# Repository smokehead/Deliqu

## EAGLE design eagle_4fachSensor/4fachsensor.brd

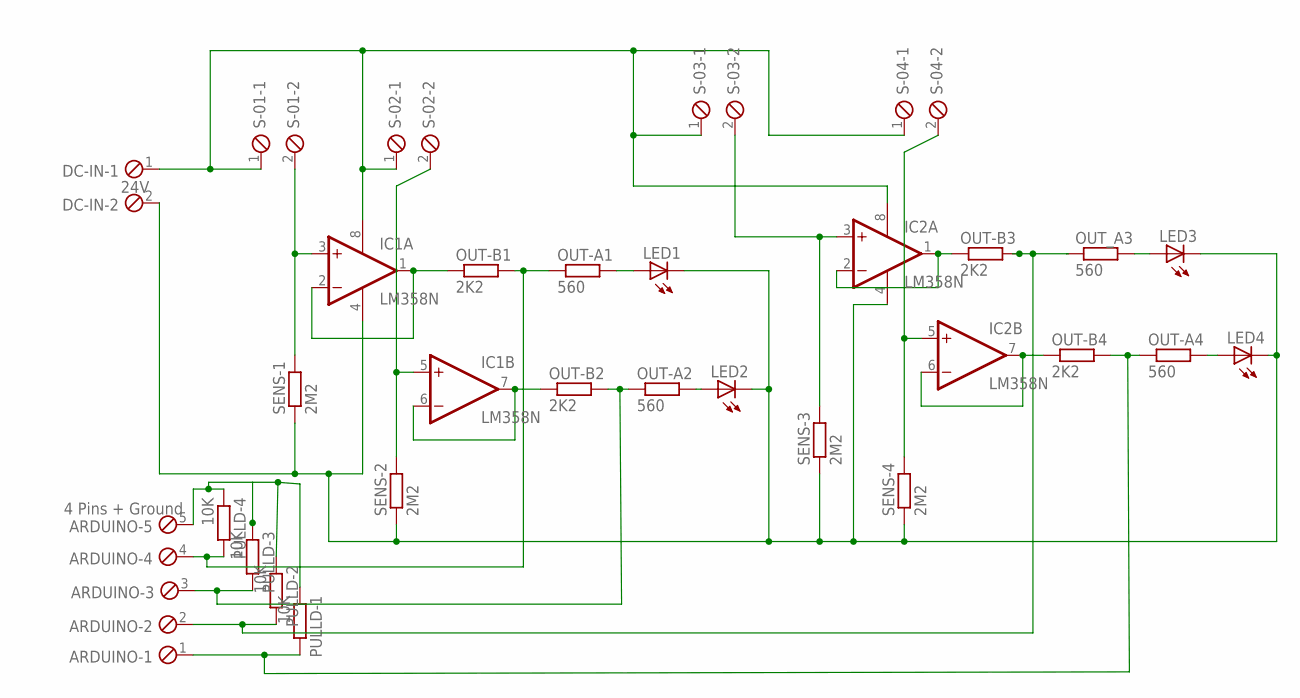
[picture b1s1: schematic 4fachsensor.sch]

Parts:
ARDUINO: 4 Pins + Ground; 5POL254
DC-IN: 24V; 2POL254
IC1, IC2: LM358N; DIL08
LED1, LED2, LED3, LED4: LED5MM
OUT-A1, OUT-A2, OUT-A4: 560; 0207/7
OUT-B1, OUT-B2, OUT-B3, OUT-B4: 2K2; 0207/7
OUT_A3: 560; 0207/7
PULLD-1, PULLD-2, PULLD-3, PULLD-4: 10K; 0207/7
S-01, S-02, S-03, S-04: MPT2; 2POL254
SENS-1, SENS-2, SENS-3, SENS-4: 2M2; 0207/7

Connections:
unnamed: DC-IN.1, IC1.8 (V+), IC2.8 (V+), S-01.1, S-02.1, S-03.1, S-04.1
unnamed: IC1.3 (+IN), S-01.2, SENS-1.2
unnamed: DC-IN.2, IC1.4 (V-), IC2.4 (V-), LED1.K (C), LED2.K (C), LED3.K (C), LED4.K (C), SENS-1.1, SENS-2.1, SENS-3.1, SENS-4.1
unnamed: IC1.1 (OUT), IC1.2 (-IN), OUT-B1.1
unnamed: LED1.A, OUT-A1.2
unnamed: IC1.6 (-IN), IC1.7 (OUT), OUT-B2.1
unnamed: IC1.5 (+IN), S-02.2, SENS-2.2
unnamed: LED2.A, OUT-A2.2
unnamed: LED4.A, OUT-A4.2
unnamed: IC2.3 (+IN), S-03.2, SENS-3.2
unnamed: IC2.5 (+IN), S-04.2, SENS-4.2
unnamed: ARDUINO.1, OUT-A4.1, OUT-B4.2, PULLD-1.2
unnamed: ARDUINO.2, OUT-B3.2, OUT_A3.1, PULLD-2.2
unnamed: IC2.1 (OUT), IC2.2 (-IN), OUT-B3.1
unnamed: IC2.6 (-IN), IC2.7 (OUT), OUT-B4.1
unnamed: ARDUINO.3, OUT-A2.1, OUT-B2.2, PULLD-3.2
unnamed: LED3.A, OUT_A3.2
unnamed: ARDUINO.4, OUT-A1.1, OUT-B1.2, PULLD-4.2
unnamed: ARDUINO.5, PULLD-1.1, PULLD-2.1, PULLD-3.1, PULLD-4.1

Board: 2 copper layers, 28 parts (0 on the bottom side), 19 nets, no tracks yet.

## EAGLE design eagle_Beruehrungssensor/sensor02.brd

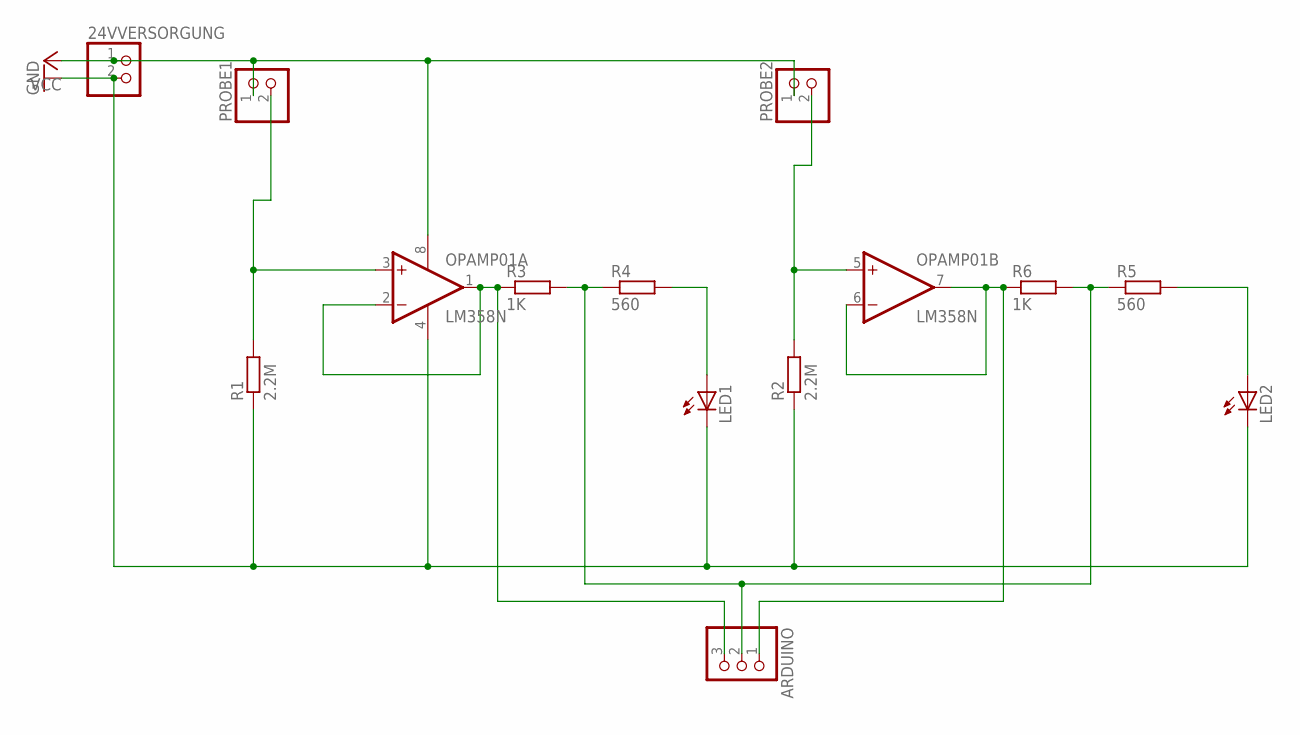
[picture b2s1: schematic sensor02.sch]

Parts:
24VVERSORGUNG: PINHD-1X2; 1X02
ARDUINO: PINHD-1X3; 1X03
LED1, LED2: LED5MM
OPAMP01: LM358N; DIL08
PROBE1, PROBE2: PINHD-1X2; 1X02
R1, R2: 2.2M; 0207/7
R3, R6: 1K; 0207/7
R4, R5: 560; 0207/7

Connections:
GND: 24VVERSORGUNG.2, LED1.K (C), LED2.K (C), OPAMP01.4 (V-), R1.1, R2.1
unnamed: OPAMP01.3 (+IN), PROBE1.2, R1.2
unnamed: OPAMP01.5 (+IN), PROBE2.2, R2.2
unnamed: ARDUINO.3, OPAMP01.1 (OUT), OPAMP01.2 (-IN), R3.1
unnamed: LED1.A, R4.2
unnamed: ARDUINO.1, OPAMP01.6 (-IN), OPAMP01.7 (OUT), R6.1
unnamed: ARDUINO.2, R3.2, R4.1, R5.1, R6.2
unnamed: LED2.A, R5.2
VCC: 24VVERSORGUNG.1, OPAMP01.8 (V+), PROBE1.1, PROBE2.1

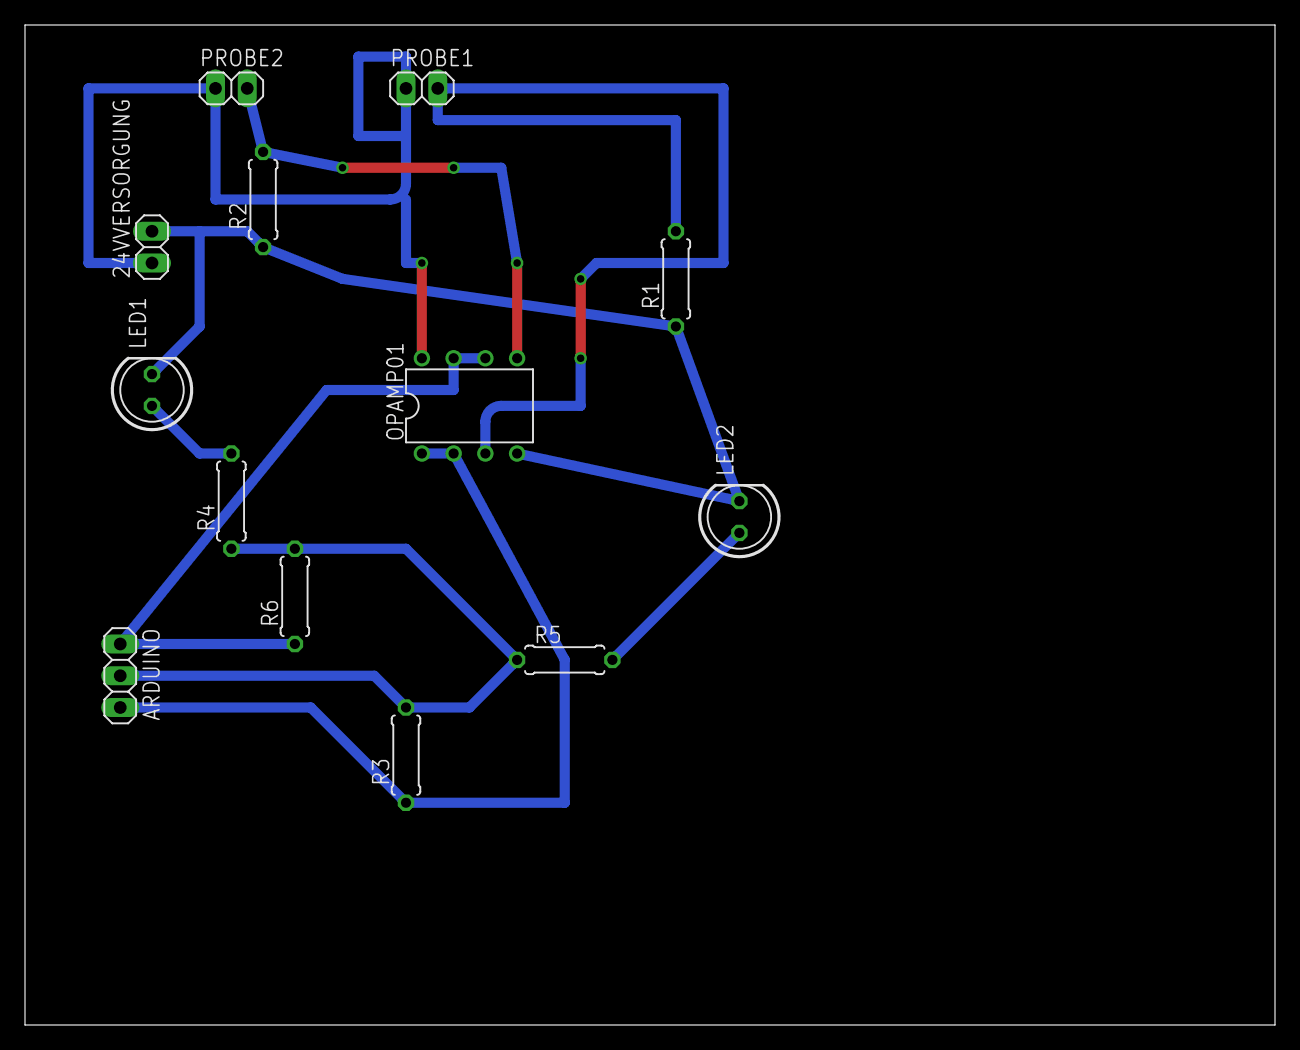
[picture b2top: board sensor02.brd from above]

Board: 2 copper layers, 100.0 x 80.0 mm, 13 parts (0 on the bottom side), 9 nets.

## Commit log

2015-07-18 Deliqueszensmessgeraet
    Ein RZL-Projekt zum Messen von Deliqueszenz mittels Arduino und einigen
    Schaltungen
2015-07-18 Schaltpläne und Scetches
    Teilprojektinformationen
2015-07-18 Komplettierung
    Fehlende Files ergänzt
2015-07-26 Ablaufplan hizugefügt
